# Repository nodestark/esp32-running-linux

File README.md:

# 🐧 ESP32 Running Linux via RISC-V Emulator
This project implements a RISC-V emulator on the ESP32 microcontroller, capable of running a minimal Linux environment.

# 📄 Overview
This project enables the execution of a lightweight Linux environment on the ESP32 by emulating RISC-V instructions. It leverages the ESP32's capabilities to support basic Linux functionalities—ideal for experimentation, learning, or running simple applications that traditionally require more robust hardware.

# ⚙️ How It Works
The emulator translates RISC-V instructions into instructions compatible with the ESP32, allowing the system to simulate a RISC-V processor environment and run a minimal Linux kernel.

# 💻 Flashing and Setup
1. Create the Filesystem Image (It's there already)

```
mklittlefs -c data -b 4096 -p 256 -s $((8*1024*1024)) littlefs.bin
```
2. Flash the Filesystem

```
esptool.py -b 1500000 write_flash 0x100000 littlefs.bin
```
3. Build and Flash the Firmware

```
idf.py flash monitor
```

> [!NOTE]
> Make sure your ESP-IDF environment is correctly set up before starting.
> Tested with ESP32-S3 and a 16MB flash configuration.
> The Linux environment is minimal and designed for embedded purposes.
> ▶️ [I'm on YouTube!](https://youtu.be/RffAsl98R4o?si=HZfnRIMDvLjHM8QV)

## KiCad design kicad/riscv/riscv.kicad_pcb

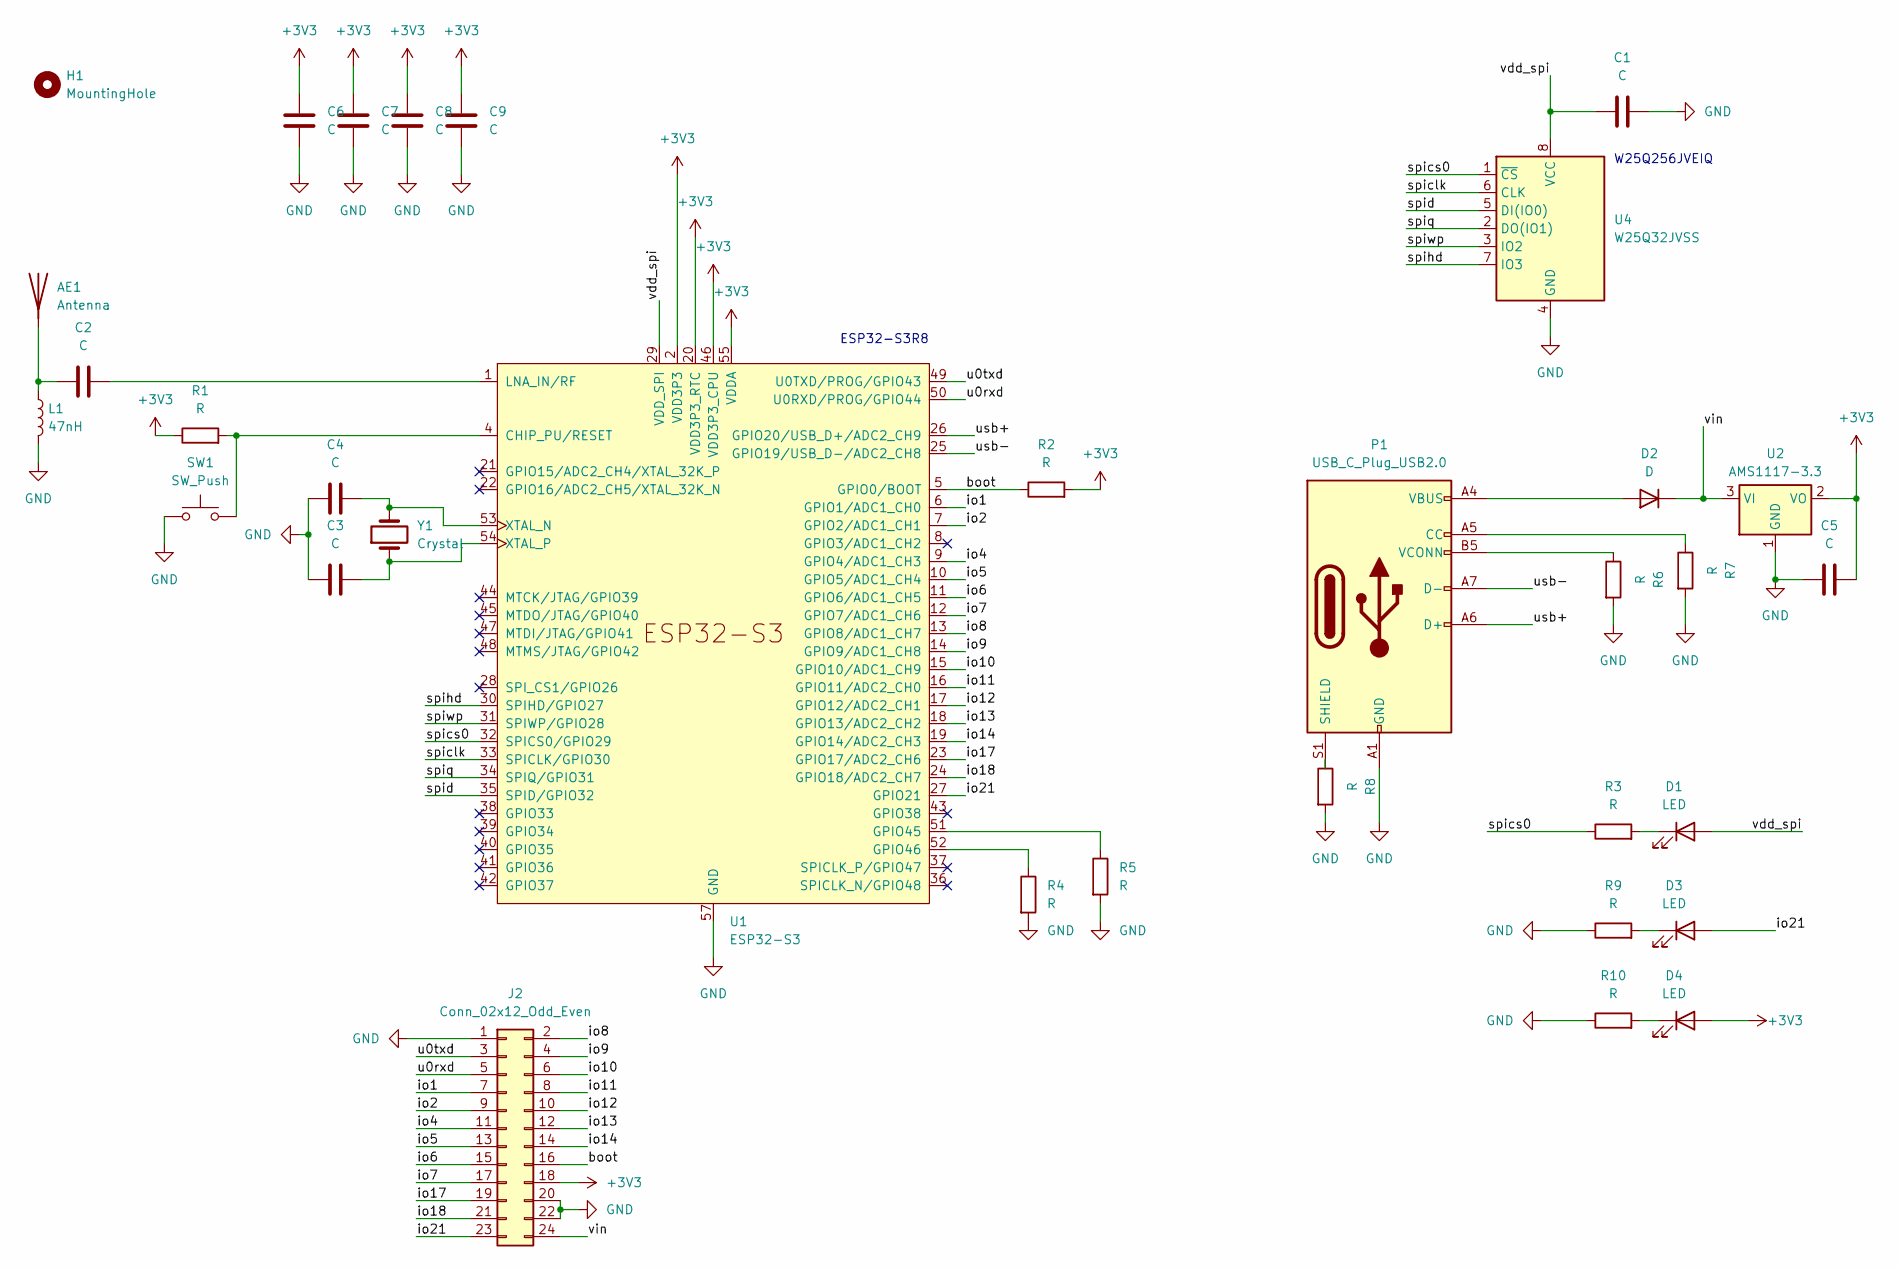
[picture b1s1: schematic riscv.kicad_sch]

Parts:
AE1: Antenna; Texas_SWRA117D_2.4GHz_Right
C1, C2, C3, C4, C5, C6, C7, C8, C9: C; C_0603_1608Metric
D1, D3, D4: LED; LED_0603_1608Metric
D2: D; D_SOD-123
H1: MountingHole; MountingHole_2.1mm
J2: Conn_02x12_Odd_Even; PinHeader_2x12_P2.54mm_Vertical
L1: 47nH; L_0603_1608Metric
P1: USB_C_Plug_USB2.0; USB_C_Receptacle_G-Switch_GT-USB-7010ASV
R1, R2, R3, R4, R5, R6, R7, R8, R9, R10: R; R_0603_1608Metric
SW1: SW_Push; SW_Tactile_SPST_NO_Straight_CK_PTS636Sx25SMTRLFS
U1: ESP32-S3; QFN-56-1EP_7x7mm_P0.4mm_EP5.6x5.6mm
U2: AMS1117-3.3; SOT-223
U4: W25Q32JVSS; WSON-8-1EP_8x6mm_P1.27mm_EP3.4x4.3mm
Y1: Crystal; Crystal_HC49-4H_Vertical

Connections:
+3V3: C5.2, C6.2, C7.2, C8.2, C9.2, D4.2 (A), J2.18, R1.1, R2.2, U1.2 (VDD3P3), U1.3 (VDD3P3), U1.20 (VDD3P3_RTC), U1.46 (VDD3P3_CPU), U1.55 (VDDA), U1.56 (VDDA), U2.2 (VO); also elsewhere on the board
/boot: J2.16, R2.1, U1.5 (GPIO0/BOOT); also elsewhere on the board
/io1: J2.7, U1.6 (GPIO1/ADC1_CH0); also elsewhere on the board
/io2: J2.9, U1.7 (GPIO2/ADC1_CH1); also elsewhere on the board
/io4: J2.11, U1.9 (GPIO4/ADC1_CH3); also elsewhere on the board
/io5: J2.13, U1.10 (GPIO5/ADC1_CH4); also elsewhere on the board
/io6: J2.15, U1.11 (GPIO6/ADC1_CH5); also elsewhere on the board
/io7: J2.17, U1.12 (GPIO7/ADC1_CH6); also elsewhere on the board
/io8: J2.2, U1.13 (GPIO8/ADC1_CH7); also elsewhere on the board
/io9: J2.4, U1.14 (GPIO9/ADC1_CH8); also elsewhere on the board
/io10: J2.6, U1.15 (GPIO10/ADC1_CH9); also elsewhere on the board
/io11: J2.8, U1.16 (GPIO11/ADC2_CH0); also elsewhere on the board
/io12: J2.10, U1.17 (GPIO12/ADC2_CH1); also elsewhere on the board
/io13: J2.12, U1.18 (GPIO13/ADC2_CH2); also elsewhere on the board
/io14: J2.14, U1.19 (GPIO14/ADC2_CH3); also elsewhere on the board
/io17: J2.19, U1.23 (GPIO17/ADC2_CH6); also elsewhere on the board
/io18: J2.21, U1.24 (GPIO18/ADC2_CH7); also elsewhere on the board
/io21: D3.2 (A), J2.23, U1.27 (GPIO21); also elsewhere on the board
/spiclk: U1.33 (SPICLK/GPIO30), U4.6 (CLK); also elsewhere on the board
/spics0: R3.1, U1.32 (SPICS0/GPIO29), U4.1 (~CS); also elsewhere on the board
/spid: U1.35 (SPID/GPIO32), U4.5 (DI(IO0)); also elsewhere on the board
/spihd: U1.30 (SPIHD/GPIO27), U4.7 (IO3); also elsewhere on the board
/spiq: U1.34 (SPIQ/GPIO31), U4.2 (DO(IO1)); also elsewhere on the board
/spiwp: U1.31 (SPIWP/GPIO28), U4.3 (IO2); also elsewhere on the board
/u0rxd: J2.5, U1.50 (U0RXD/PROG/GPIO44); also elsewhere on the board
/u0txd: J2.3, U1.49 (U0TXD/PROG/GPIO43); also elsewhere on the board
/usb+: P1.A6 (D+), U1.26 (GPIO20/USB_D+/ADC2_CH9); also elsewhere on the board
/usb-: P1.A7 (D-), U1.25 (GPIO19/USB_D-/ADC2_CH8); also elsewhere on the board
/vdd_spi: C1.1, D1.2 (A), U1.29 (VDD_SPI), U4.8 (VCC); also elsewhere on the board
/vin: D2.1 (K), J2.24, U2.3 (VI)
GND: C1.2, C3.1, C4.1, C5.1, C6.1, C7.1, C8.1, C9.1, J2.1, J2.20, J2.22, L1.2, P1.A1 (GND), P1.A12 (GND), P1.B1 (GND), P1.B12 (GND), R4.2, R5.2, R6.2, R7.2, R8.2, R9.1, R10.1, SW1.1, U1.57 (GND), U2.1 (GND), U4.4 (GND); also elsewhere on the board
unnamed: AE1.1 (A), C2.1, L1.1
unnamed: D1.1 (K), R3.2
unnamed: D2.2 (A), P1.A4 (VBUS), P1.A9 (VBUS), P1.B4 (VBUS), P1.B9 (VBUS)
unnamed: D3.1 (K), R9.2
unnamed: D4.1 (K), R10.2
unnamed: P1.A5 (CC), R7.1
unnamed: P1.S1 (SHIELD), R8.1
unnamed: P1.B5 (VCONN), R6.1
unnamed 39: R1.2, SW1.2, U1.4 (CHIP_PU/RESET); also elsewhere on the board
unnamed 40: R5.1, U1.51 (GPIO45); also elsewhere on the board
unnamed 41: R4.1, U1.52 (GPIO46); also elsewhere on the board
unnamed 42: C2.2, U1.1 (LNA_IN/RF); also elsewhere on the board
unnamed 43: C4.2, U1.53 (XTAL_N), Y1.2; also elsewhere on the board
unnamed 44: C3.2, U1.54 (XTAL_P), Y1.1; also elsewhere on the board

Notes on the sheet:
W25Q256JVEIQ
ESP32-S3R8

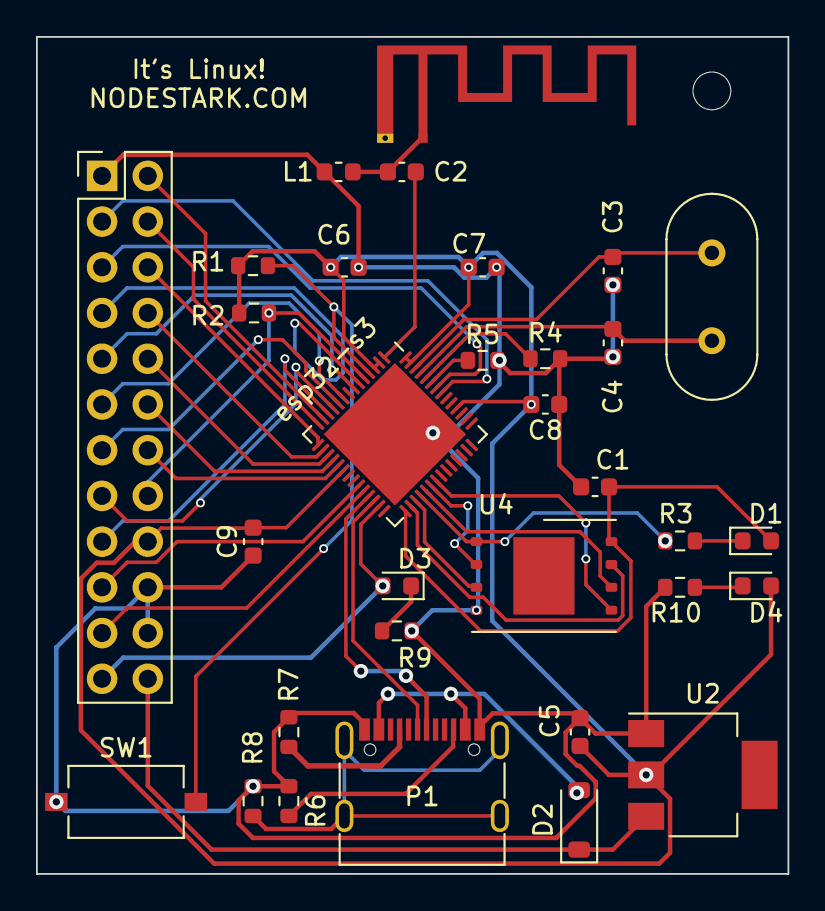
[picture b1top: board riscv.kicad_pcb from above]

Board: 2 copper layers, 41.8 x 46.5 mm, 33 parts (0 on the bottom side), 45 nets.

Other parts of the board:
esp32-s3: ESP32-S3; QFN-56-1EP_7x7mm_P0.4mm_EP5.6x5.6mm

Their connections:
+3V3: esp32-s3.2 (VDD3P3), esp32-s3.3 (VDD3P3), esp32-s3.20 (VDD3P3_RTC), esp32-s3.46 (VDD3P3_CPU), esp32-s3.55 (VDDA), esp32-s3.56 (VDDA); also elsewhere on the board
/boot: esp32-s3.5 (GPIO0/BOOT); also elsewhere on the board
/io1: esp32-s3.6 (GPIO1/ADC1_CH0); also elsewhere on the board
/io2: esp32-s3.7 (GPIO2/ADC1_CH1); also elsewhere on the board
/io4: esp32-s3.9 (GPIO4/ADC1_CH3); also elsewhere on the board
/io5: esp32-s3.10 (GPIO5/ADC1_CH4); also elsewhere on the board
/io6: esp32-s3.11 (GPIO6/ADC1_CH5); also elsewhere on the board
/io7: esp32-s3.12 (GPIO7/ADC1_CH6); also elsewhere on the board
/io8: esp32-s3.13 (GPIO8/ADC1_CH7); also elsewhere on the board
/io9: esp32-s3.14 (GPIO9/ADC1_CH8); also elsewhere on the board
/io10: esp32-s3.15 (GPIO10/ADC1_CH9); also elsewhere on the board
/io11: esp32-s3.16 (GPIO11/ADC2_CH0); also elsewhere on the board
/io12: esp32-s3.17 (GPIO12/ADC2_CH1); also elsewhere on the board
/io13: esp32-s3.18 (GPIO13/ADC2_CH2); also elsewhere on the board
/io14: esp32-s3.19 (GPIO14/ADC2_CH3); also elsewhere on the board
/io17: esp32-s3.23 (GPIO17/ADC2_CH6); also elsewhere on the board
/io18: esp32-s3.24 (GPIO18/ADC2_CH7); also elsewhere on the board
/io21: esp32-s3.27 (GPIO21); also elsewhere on the board
/spiclk: esp32-s3.33 (SPICLK/GPIO30); also elsewhere on the board
/spics0: esp32-s3.32 (SPICS0/GPIO29); also elsewhere on the board
/spid: esp32-s3.35 (SPID/GPIO32); also elsewhere on the board
/spihd: esp32-s3.30 (SPIHD/GPIO27); also elsewhere on the board
/spiq: esp32-s3.34 (SPIQ/GPIO31); also elsewhere on the board
/spiwp: esp32-s3.31 (SPIWP/GPIO28); also elsewhere on the board
/u0rxd: esp32-s3.50 (U0RXD/PROG/GPIO44); also elsewhere on the board
/u0txd: esp32-s3.49 (U0TXD/PROG/GPIO43); also elsewhere on the board
/usb+: esp32-s3.26 (GPIO20/USB_D+/ADC2_CH9); also elsewhere on the board
/usb-: esp32-s3.25 (GPIO19/USB_D-/ADC2_CH8); also elsewhere on the board
/vdd_spi: esp32-s3.29 (VDD_SPI); also elsewhere on the board
GND: esp32-s3.57 (GND); also elsewhere on the board
unnamed 39: esp32-s3.4 (CHIP_PU/RESET); also elsewhere on the board
unnamed 40: esp32-s3.51 (GPIO45); also elsewhere on the board
unnamed 41: esp32-s3.52 (GPIO46); also elsewhere on the board
unnamed 42: esp32-s3.1 (LNA_IN/RF); also elsewhere on the board
unnamed 43: esp32-s3.53 (XTAL_N); also elsewhere on the board
unnamed 44: esp32-s3.54 (XTAL_P); also elsewhere on the board

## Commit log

2024-07-24 Initial import
2024-07-24 Refacting
2025-03-24 Implementing buildroot-2022.05 Dockerfiile
2025-03-24 Removing not used image
2025-03-24 Refacting paths
2025-05-07 Refacting project
2025-05-07 Test merge request
2025-10-02 USB Serial/JTAG
